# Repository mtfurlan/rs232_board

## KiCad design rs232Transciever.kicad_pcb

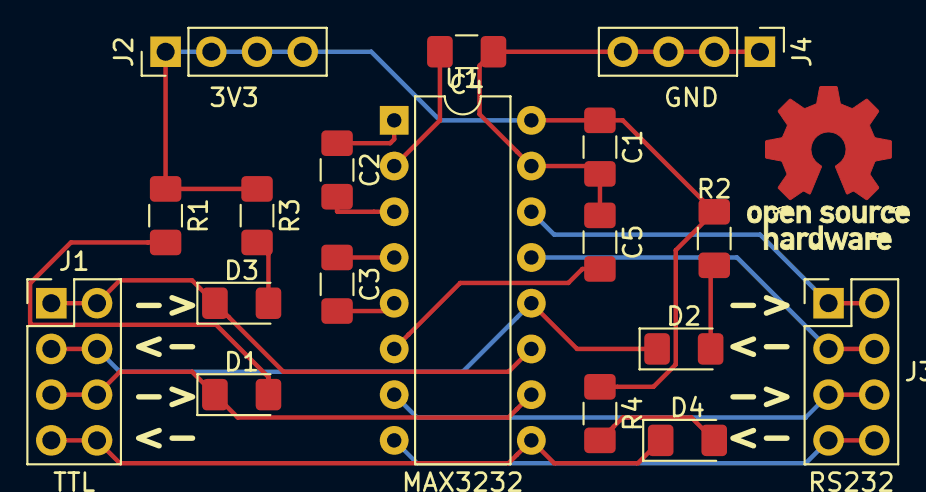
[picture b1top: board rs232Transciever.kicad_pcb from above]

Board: 2 copper layers, 19 parts (0 on the bottom side), 20 nets.

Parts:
C1, C2: .1uF; C_1206_3216Metric_Pad1.42x1.75mm_HandSolder
C3, C4, C5: .47uF; C_1206_3216Metric_Pad1.42x1.75mm_HandSolder
D1, D2, D3, D4: LED; LED_1206_3216Metric_Pad1.42x1.75mm_HandSolder
J1: TTL; PinHeader_2x04_P2.54mm_Vertical
J2: 3V3; PinHeader_1x04_P2.54mm_Vertical
J3: RS232; PinHeader_2x04_P2.54mm_Vertical
J4: GND; PinHeader_1x04_P2.54mm_Vertical
R1, R2, R3, R4: 1k; R_1206_3216Metric_Pad1.42x1.75mm_HandSolder
U1: MAX3232; DIP-16_W7.62mm
oshw: G***; oshw-logo

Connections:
+3V3: C1.1, J2.1, J2.2, J2.3, J2.4, R1.1, R2.1, R3.1, R4.1, U1.16
GND: C1.2, C4.1, C5.1, J4.1, J4.2, J4.3, J4.4, U1.15
unnamed: C2.1, U1.1
unnamed: C2.2, U1.3
unnamed: C3.1, U1.4
unnamed: C3.2, U1.5
unnamed: C4.2, U1.2
unnamed: C5.2, U1.6
unnamed: D1.1, J1.5, J1.6, U1.10
unnamed: D1.2, R1.2
unnamed: D2.1, J1.3, J1.4, U1.12
unnamed: D2.2, R2.2
unnamed: D3.1, J1.1, J1.2, U1.11
unnamed: D3.2, R3.2
unnamed: D4.1, J1.7, J1.8, U1.9
unnamed: D4.2, R4.2
unnamed: J3.1, J3.2, U1.14
unnamed: J3.3, J3.4, U1.13
unnamed: J3.5, J3.6, U1.7
unnamed: J3.7, J3.8, U1.8

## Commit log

2019-07-12 has OSHW logo and LEDs
